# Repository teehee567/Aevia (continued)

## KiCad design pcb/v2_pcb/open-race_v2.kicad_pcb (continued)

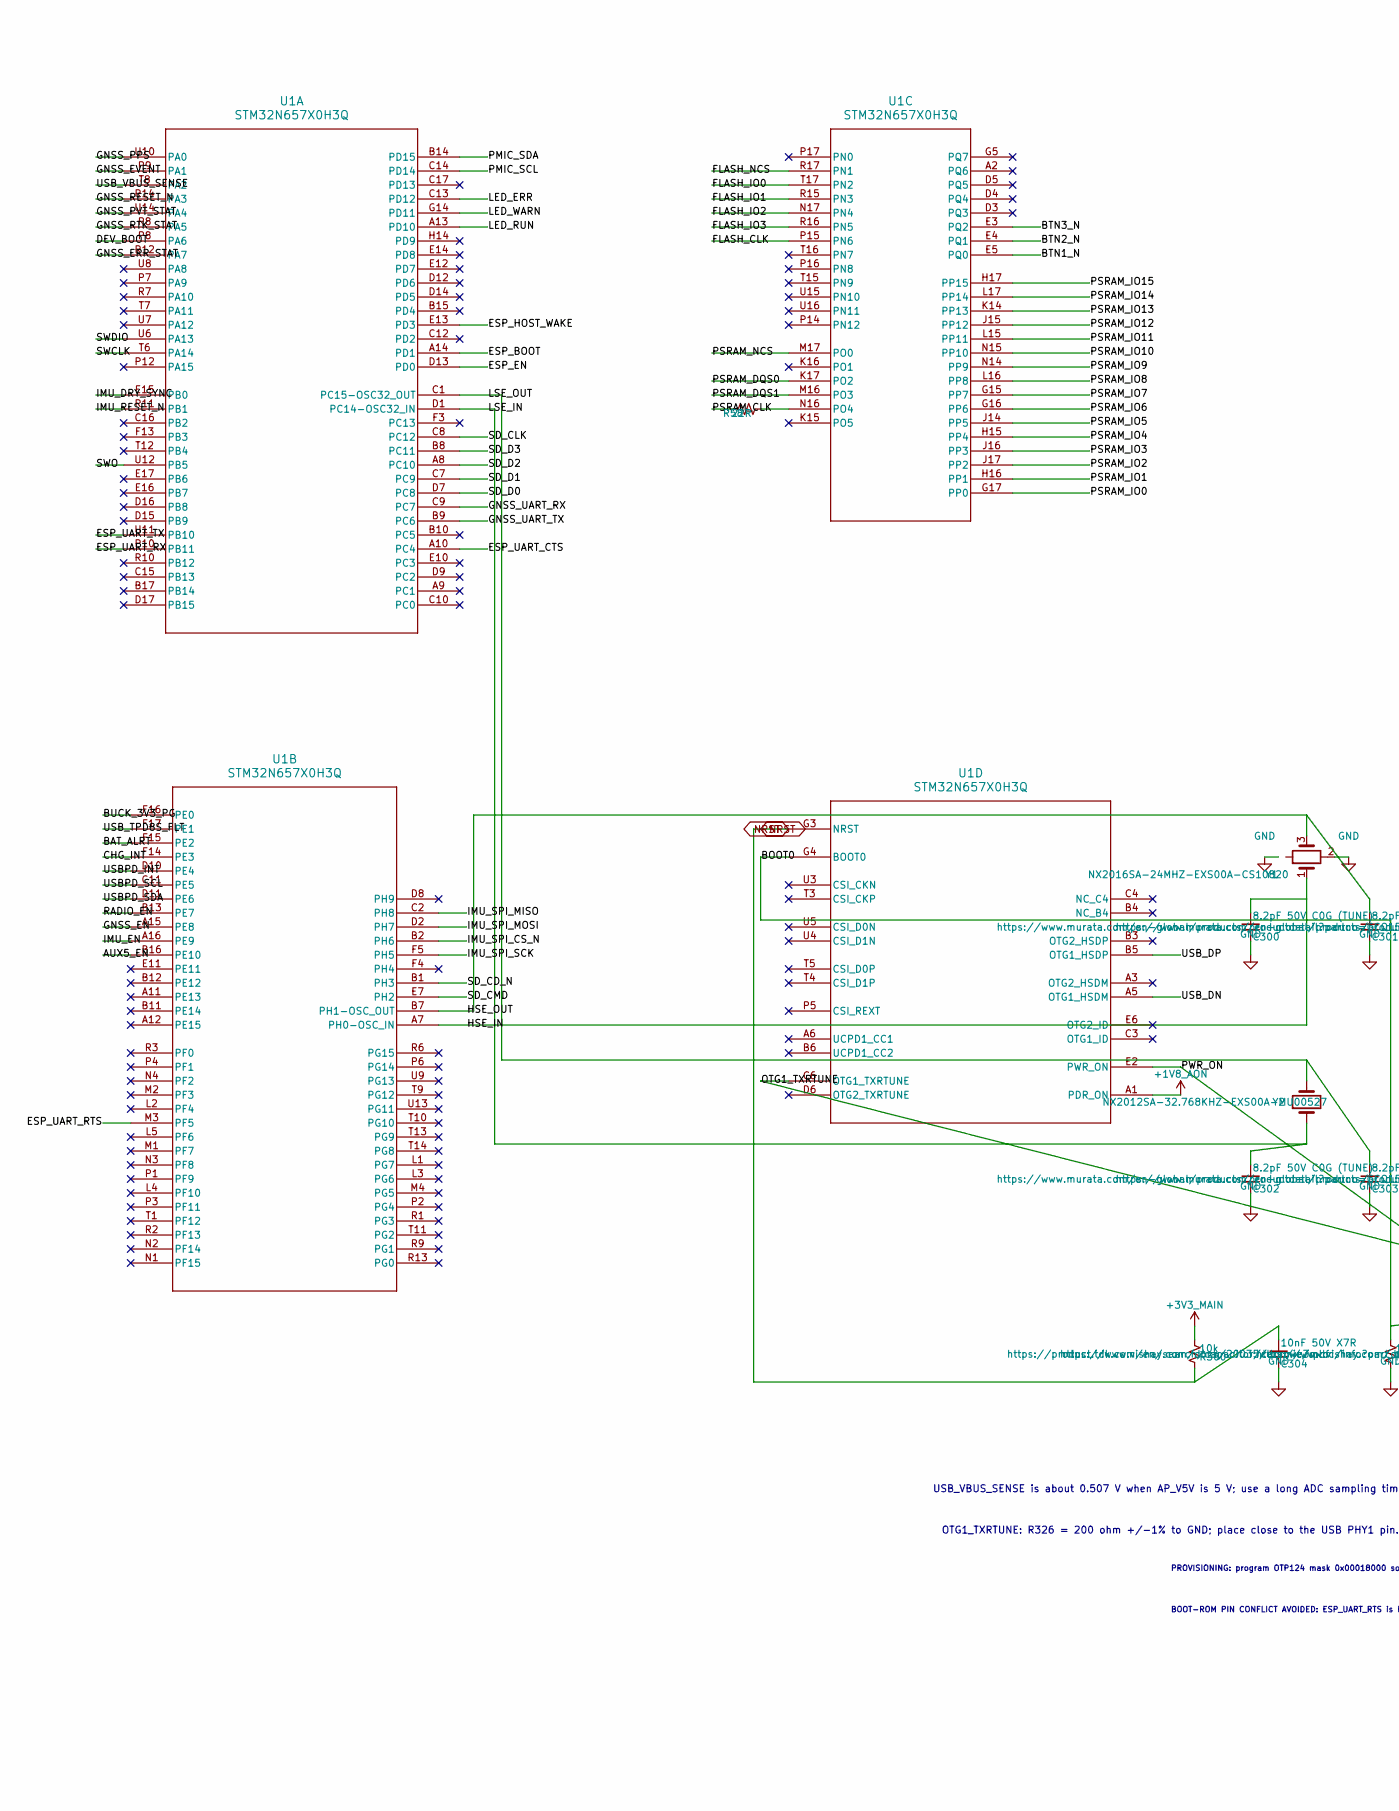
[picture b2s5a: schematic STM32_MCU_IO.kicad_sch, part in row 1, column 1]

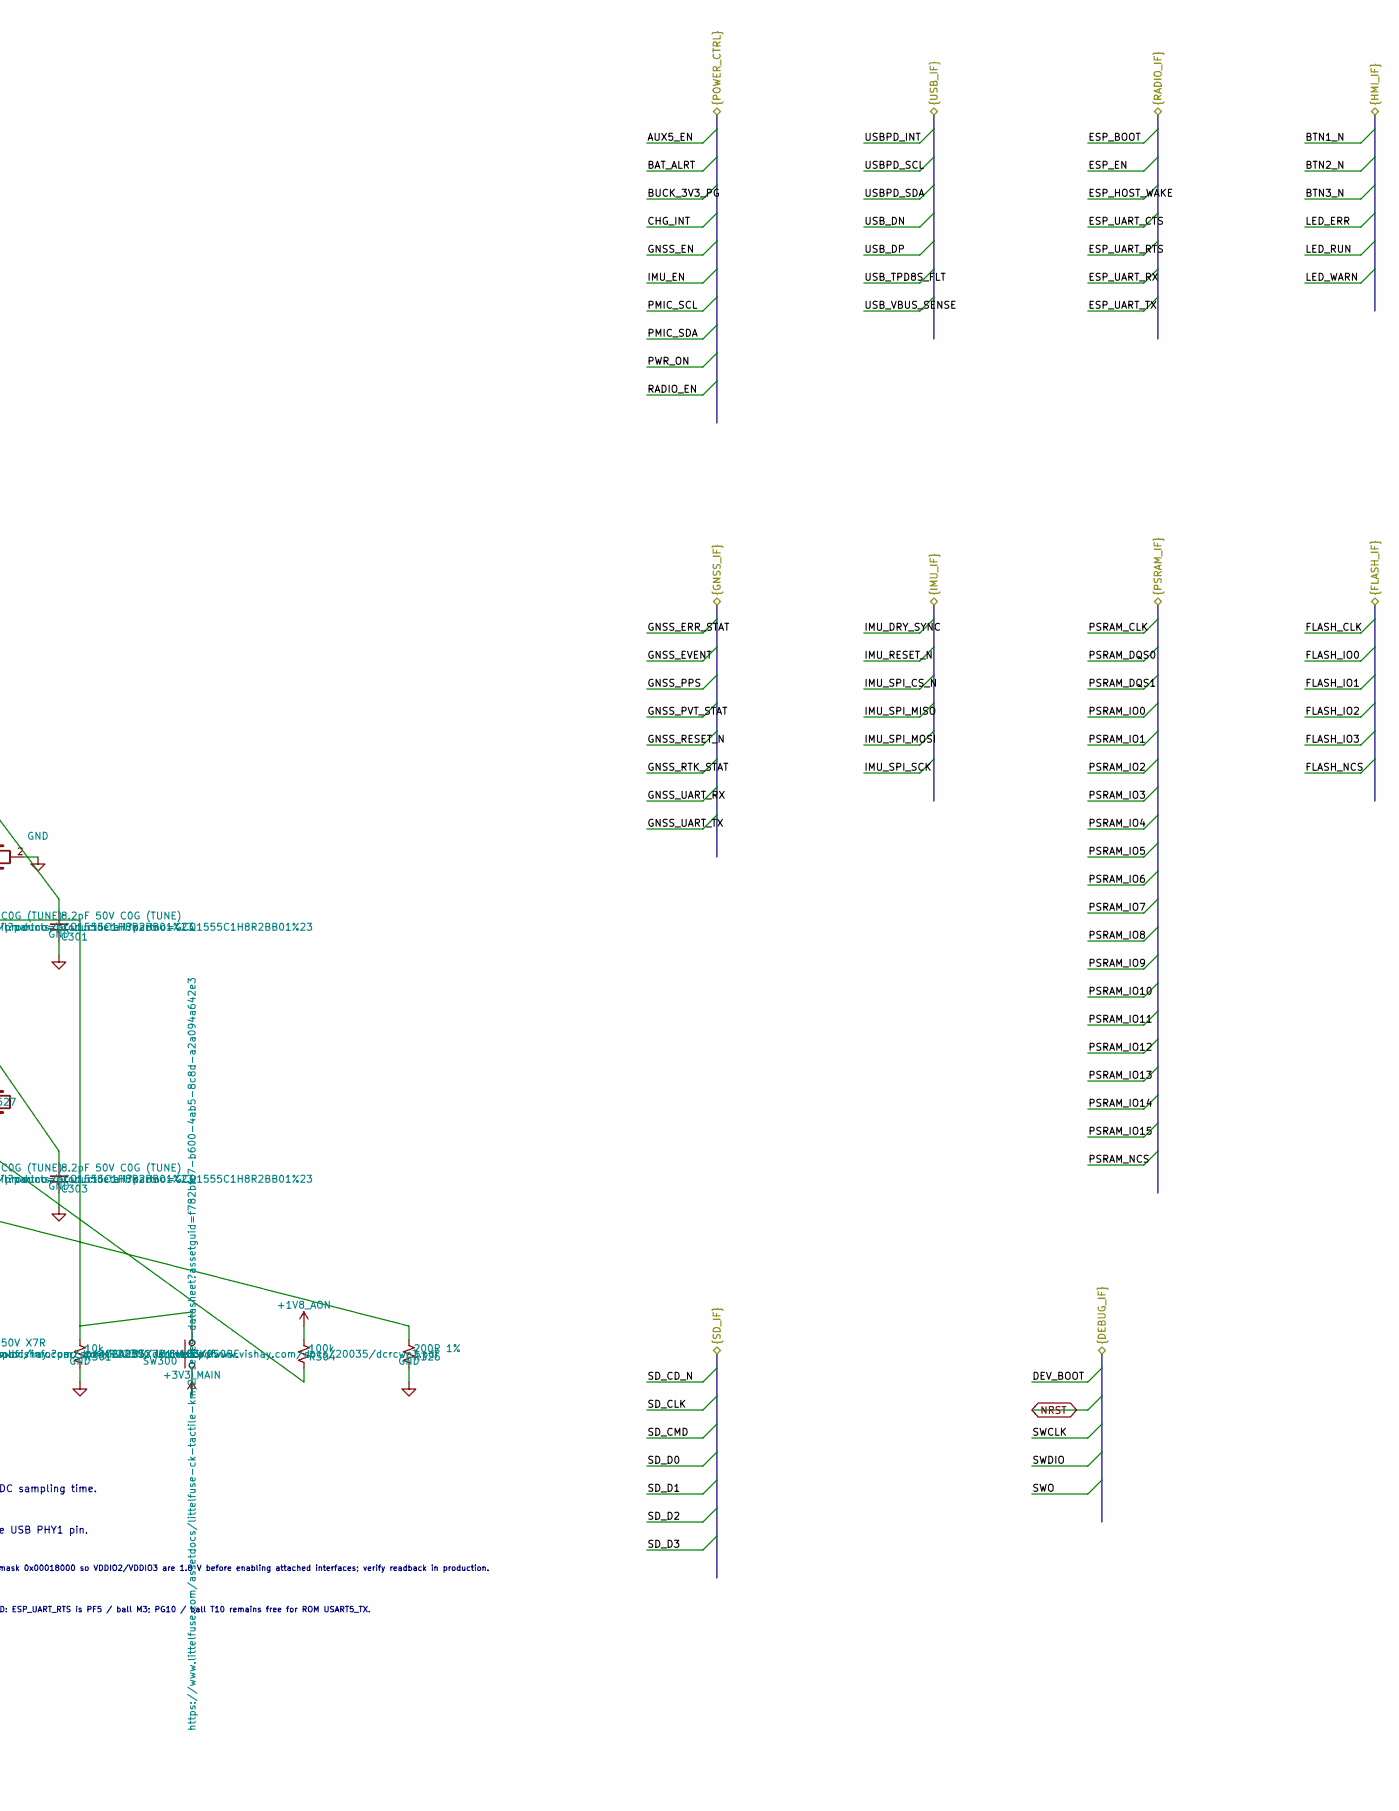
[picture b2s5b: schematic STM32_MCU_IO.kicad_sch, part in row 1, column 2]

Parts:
C300, C301, C302, C303: 8.2pF 50V C0G (TUNE); C_0402_1005Metric; Voltage 50 VDC; Tolerance ±0.1 pF; MPN GCQ1555C1H8R2BB01D
C304: 10nF 50V X7R; C_0402_1005Metric; Voltage 50 VDC; Tolerance ±10%; MPN CGA2B3X7R1H103K050BE
R58: 22R; R_0402_1005Metric; Tolerance ±1%; MPN CRCW040222R0FKED
R300, R301: 10k; R_0402_1005Metric; Tolerance ±1%; MPN CRCW040210K0FKED
R304: 100k; R_0402_1005Metric; Tolerance ±1%; MPN CRCW0402100KFKED
R326: 200R 1%; R_0402_1005Metric; Tolerance ±1%; MPN CRCW0402200RFKED
SW300: KMR223NG ULC LFG; SW_Push_1P1T_NO_CK_KMR2; MPN Y78B22324FP
U1: STM32N657X0H3Q; VFBGA264_14X14_STM; MPN STM32N657X0H3Q
Y1: NX2016SA-24MHZ-EXS00A-CS10820; Crystal_SMD_2016-4Pin_2.0x1.6mm; MPN NX2016SA-24MHZ-EXS00A-CS10820
Y2: NX2012SA-32.768KHZ-EXS00A-MU00527; Crystal_SMD_2012-2Pin_2.0x1.2mm; MPN NX2012SA-32.768KHZ-EXS00A-MU00527

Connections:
+1V8_AON: R304.1, U1.A1 (PDR_ON); also elsewhere on the board
/Buttons and LEDs/BTN1_N: U1.E5 (PQ0); also elsewhere on the board
/Buttons and LEDs/BTN2_N: U1.E4 (PQ1); also elsewhere on the board
/Buttons and LEDs/BTN3_N: U1.E3 (PQ2); also elsewhere on the board
/Buttons and LEDs/LED_ERR: U1.C13 (PD12); also elsewhere on the board
/Buttons and LEDs/LED_RUN: U1.A13 (PD10); also elsewhere on the board
/Buttons and LEDs/LED_WARN: U1.G14 (PD11); also elsewhere on the board
/ESP32-C6 radio/ESP_BOOT: U1.A14 (PD1); also elsewhere on the board
/ESP32-C6 radio/ESP_EN: U1.D13 (PD0); also elsewhere on the board
/ESP32-C6 radio/ESP_HOST_WAKE: U1.E13 (PD3); also elsewhere on the board
/ESP32-C6 radio/ESP_UART_CTS: U1.A10 (PC4); also elsewhere on the board
/ESP32-C6 radio/ESP_UART_RTS: U1.M3 (PF5); also elsewhere on the board
/ESP32-C6 radio/ESP_UART_RX: U1.P10 (PB11); also elsewhere on the board
/ESP32-C6 radio/ESP_UART_TX: U1.U11 (PB10); also elsewhere on the board
/Power/AUX5_EN: U1.B16 (PE10); also elsewhere on the board
/Power/BAT_ALRT: U1.F15 (PE2); also elsewhere on the board
/Power/BUCK_3V3_PG: U1.F16 (PE0); also elsewhere on the board
/Power/CHG_INT: U1.F14 (PE3); also elsewhere on the board
/Power/GNSS_EN: U1.A15 (PE8); also elsewhere on the board
/Power/IMU_EN: U1.A16 (PE9); also elsewhere on the board
/Power/PMIC_SCL: U1.C14 (PD14); also elsewhere on the board
/Power/PMIC_SDA: U1.B14 (PD15); also elsewhere on the board
/Power/PWR_ON: R304.2, U1.E2 (PWR_ON); also elsewhere on the board
/Power/RADIO_EN: U1.B13 (PE7); also elsewhere on the board
/Quad boot flash/FLASH_CLK: U1.P15 (PN6); also elsewhere on the board
/Quad boot flash/FLASH_IO0: U1.T17 (PN2); also elsewhere on the board
/Quad boot flash/FLASH_IO1: U1.R15 (PN3); also elsewhere on the board
/Quad boot flash/FLASH_IO2: U1.N17 (PN4); also elsewhere on the board
/Quad boot flash/FLASH_IO3: U1.R16 (PN5); also elsewhere on the board
/Quad boot flash/FLASH_NCS: U1.R17 (PN1); also elsewhere on the board
/SCH16T IMU/IMU_DRY_SYNC: U1.E15 (PB0); also elsewhere on the board
/SCH16T IMU/IMU_RESET_N: U1.R11 (PB1); also elsewhere on the board
/SCH16T IMU/IMU_SPI_CS_N: U1.B2 (PH6); also elsewhere on the board
/SCH16T IMU/IMU_SPI_MISO: U1.C2 (PH8); also elsewhere on the board
/SCH16T IMU/IMU_SPI_MOSI: U1.D2 (PH7); also elsewhere on the board
/SCH16T IMU/IMU_SPI_SCK: U1.F5 (PH5); also elsewhere on the board
/STM32 MCU IO/BOOT0: R301.1, SW300.2, U1.G4 (BOOT0)
/STM32 MCU IO/DEV_BOOT: U1.P8 (PA6); also elsewhere on the board
/STM32 MCU IO/GNSS_ERR_STAT: U1.R12 (PA7); also elsewhere on the board
/STM32 MCU IO/GNSS_EVENT: U1.P9 (PA1); also elsewhere on the board
/STM32 MCU IO/GNSS_PPS: U1.U10 (PA0); also elsewhere on the board
/STM32 MCU IO/GNSS_PVT_STAT: U1.U14 (PA4); also elsewhere on the board
/STM32 MCU IO/GNSS_RESET_N: U1.R14 (PA3); also elsewhere on the board
/STM32 MCU IO/GNSS_RTK_STAT: U1.R8 (PA5); also elsewhere on the board
/STM32 MCU IO/GNSS_UART_RX: U1.C9 (PC7); also elsewhere on the board
/STM32 MCU IO/GNSS_UART_TX: U1.B9 (PC6); also elsewhere on the board
/STM32 MCU IO/HSE_IN: C300.1, U1.A7 (PH0-OSC_IN), Y1.1
/STM32 MCU IO/HSE_OUT: C301.1, U1.B7 (PH1-OSC_OUT), Y1.3
/STM32 MCU IO/LSE_IN: C302.1, U1.D1 (PC14-OSC32_IN), Y2.1
/STM32 MCU IO/LSE_OUT: C303.1, U1.C1 (PC15-OSC32_OUT), Y2.2
/STM32 MCU IO/PSRAM_CLK: R58.1; also elsewhere on the board
/STM32 MCU IO/PSRAM_DQS0: U1.K17 (PO2); also elsewhere on the board
/STM32 MCU IO/PSRAM_DQS1: U1.M16 (PO3); also elsewhere on the board
/STM32 MCU IO/PSRAM_IO0: U1.G17 (PP0); also elsewhere on the board
/STM32 MCU IO/PSRAM_IO1: U1.H16 (PP1); also elsewhere on the board
/STM32 MCU IO/PSRAM_IO2: U1.J17 (PP2); also elsewhere on the board
/STM32 MCU IO/PSRAM_IO3: U1.J16 (PP3); also elsewhere on the board
/STM32 MCU IO/PSRAM_IO4: U1.H15 (PP4); also elsewhere on the board
/STM32 MCU IO/PSRAM_IO5: U1.J14 (PP5); also elsewhere on the board
/STM32 MCU IO/PSRAM_IO6: U1.G16 (PP6); also elsewhere on the board
/STM32 MCU IO/PSRAM_IO7: U1.G15 (PP7); also elsewhere on the board
/STM32 MCU IO/PSRAM_IO8: U1.L16 (PP8); also elsewhere on the board
/STM32 MCU IO/PSRAM_IO9: U1.N14 (PP9); also elsewhere on the board
/STM32 MCU IO/PSRAM_IO10: U1.N15 (PP10); also elsewhere on the board
/STM32 MCU IO/PSRAM_IO11: U1.L15 (PP11); also elsewhere on the board
/STM32 MCU IO/PSRAM_IO12: U1.J15 (PP12); also elsewhere on the board
/STM32 MCU IO/PSRAM_IO13: U1.K14 (PP13); also elsewhere on the board
/STM32 MCU IO/PSRAM_IO14: U1.L17 (PP14); also elsewhere on the board
/STM32 MCU IO/PSRAM_IO15: U1.H17 (PP15); also elsewhere on the board
/STM32 MCU IO/PSRAM_NCS: U1.M17 (PO0); also elsewhere on the board
/STM32 MCU IO/SD_CD_N: U1.B1 (PH3); also elsewhere on the board
/STM32 MCU IO/SD_CLK: U1.C8 (PC12); also elsewhere on the board
/STM32 MCU IO/SD_CMD: U1.E7 (PH2); also elsewhere on the board
/STM32 MCU IO/SD_D0: U1.D7 (PC8); also elsewhere on the board
/STM32 MCU IO/SD_D1: U1.C7 (PC9); also elsewhere on the board
/STM32 MCU IO/SD_D2: U1.A8 (PC10); also elsewhere on the board
/STM32 MCU IO/SD_D3: U1.B8 (PC11); also elsewhere on the board
/STM32 MCU IO/SWCLK: U1.T6 (PA14); also elsewhere on the board
/STM32 MCU IO/SWDIO: U1.U6 (PA13); also elsewhere on the board
/STM32 MCU IO/SWO: U1.U12 (PB5); also elsewhere on the board
/STM32 MCU IO/USBPD_INT: U1.D10 (PE4); also elsewhere on the board
/STM32 MCU IO/USBPD_SCL: U1.C11 (PE5); also elsewhere on the board
/STM32 MCU IO/USBPD_SDA: U1.D11 (PE6); also elsewhere on the board
/STM32 MCU IO/USB_DN: U1.A5 (OTG1_HSDM); also elsewhere on the board
/STM32 MCU IO/USB_DP: U1.B5 (OTG1_HSDP); also elsewhere on the board
/STM32 MCU IO/USB_TPD8S_FLT: U1.F17 (PE1); also elsewhere on the board
/STM32 MCU IO/USB_VBUS_SENSE: U1.T8 (PA2); also elsewhere on the board
NRST: C304.1, R300.2, U1.G3 (NRST); also elsewhere on the board
unnamed: R58.2, U1.N16 (PO4)

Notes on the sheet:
BOOT-ROM PIN CONFLICT AVOIDED: ESP_UART_RTS is PF5 / ball M3; PG10 / ball T10 remains free for ROM USART5_TX.
PROVISIONING: program OTP124 mask 0x00018000 so VDDIO2/VDDIO3 are 1.8 V before enabling attached interfaces; verify readback in production.
OTG1_TXRTUNE: R326 = 200 ohm +/-1% to GND; place close to the USB PHY1 pin.
USB_VBUS_SENSE is about 0.507 V when AP_V5V is 5 V; use a long ADC sampling time.

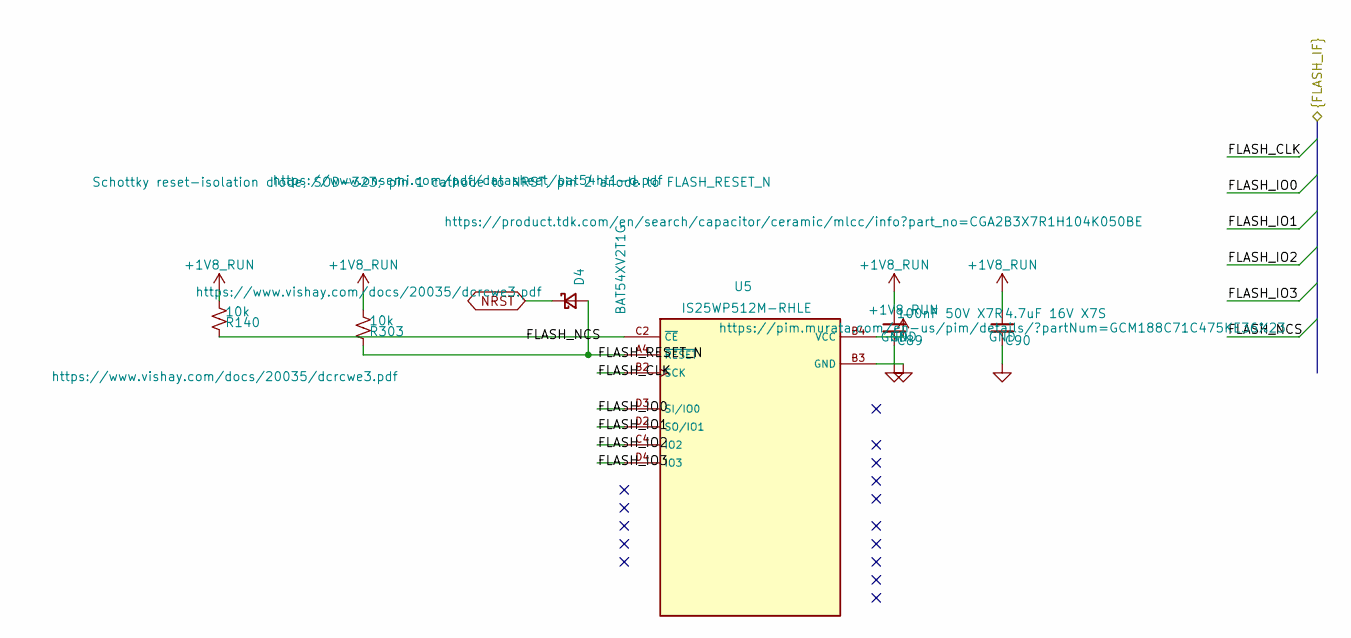
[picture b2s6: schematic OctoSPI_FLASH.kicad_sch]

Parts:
C89: 100nF 50V X7R; C_0402_1005Metric; Voltage 50 VDC; Tolerance ±10%; MPN CGA2B3X7R1H104K050BE
C90: 4.7uF 16V X7S; C_0603_1608Metric; Voltage 16 VDC; Tolerance ±10%; MPN GCM188C71C475KE36D
D4: BAT54XV2T1G; D_SOD-523; MPN BAT54HT1G
R140, R303: 10k; R_0402_1005Metric; Tolerance ±1%; MPN CRCW040210K0FKED
U5: IS25WP512M-RHLE; BGA24C100P5X5_800X600X120; MPN IS25WP512M-RHLE

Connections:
+1V8_RUN: C89.1, C90.1, R140.1, R303.1, U5.B4 (VCC); also elsewhere on the board
/Quad boot flash/FLASH_CLK: U5.B2 (SCK); also elsewhere on the board
/Quad boot flash/FLASH_IO0: U5.D3 (SI/IO0); also elsewhere on the board
/Quad boot flash/FLASH_IO1: U5.D2 (SO/IO1); also elsewhere on the board
/Quad boot flash/FLASH_IO2: U5.C4 (IO2); also elsewhere on the board
/Quad boot flash/FLASH_IO3: U5.D4 (IO3); also elsewhere on the board
/Quad boot flash/FLASH_NCS: R140.2, U5.C2 (~CE); also elsewhere on the board
/Quad boot flash/FLASH_RESET_N: D4.2 (A), R303.2, U5.A4 (~RESET)
NRST: D4.1 (K); also elsewhere on the board

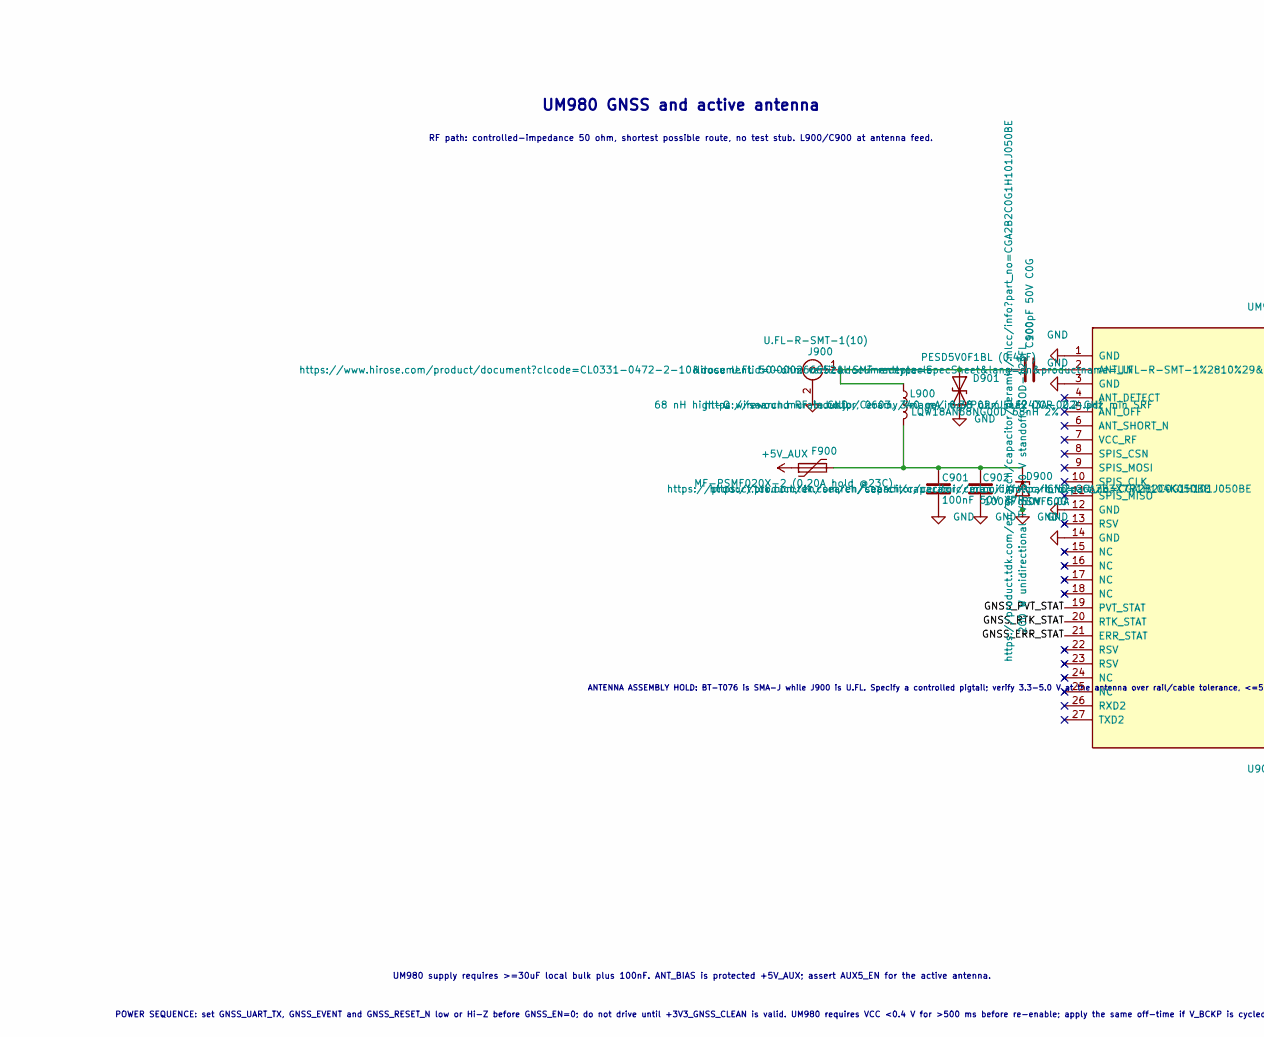
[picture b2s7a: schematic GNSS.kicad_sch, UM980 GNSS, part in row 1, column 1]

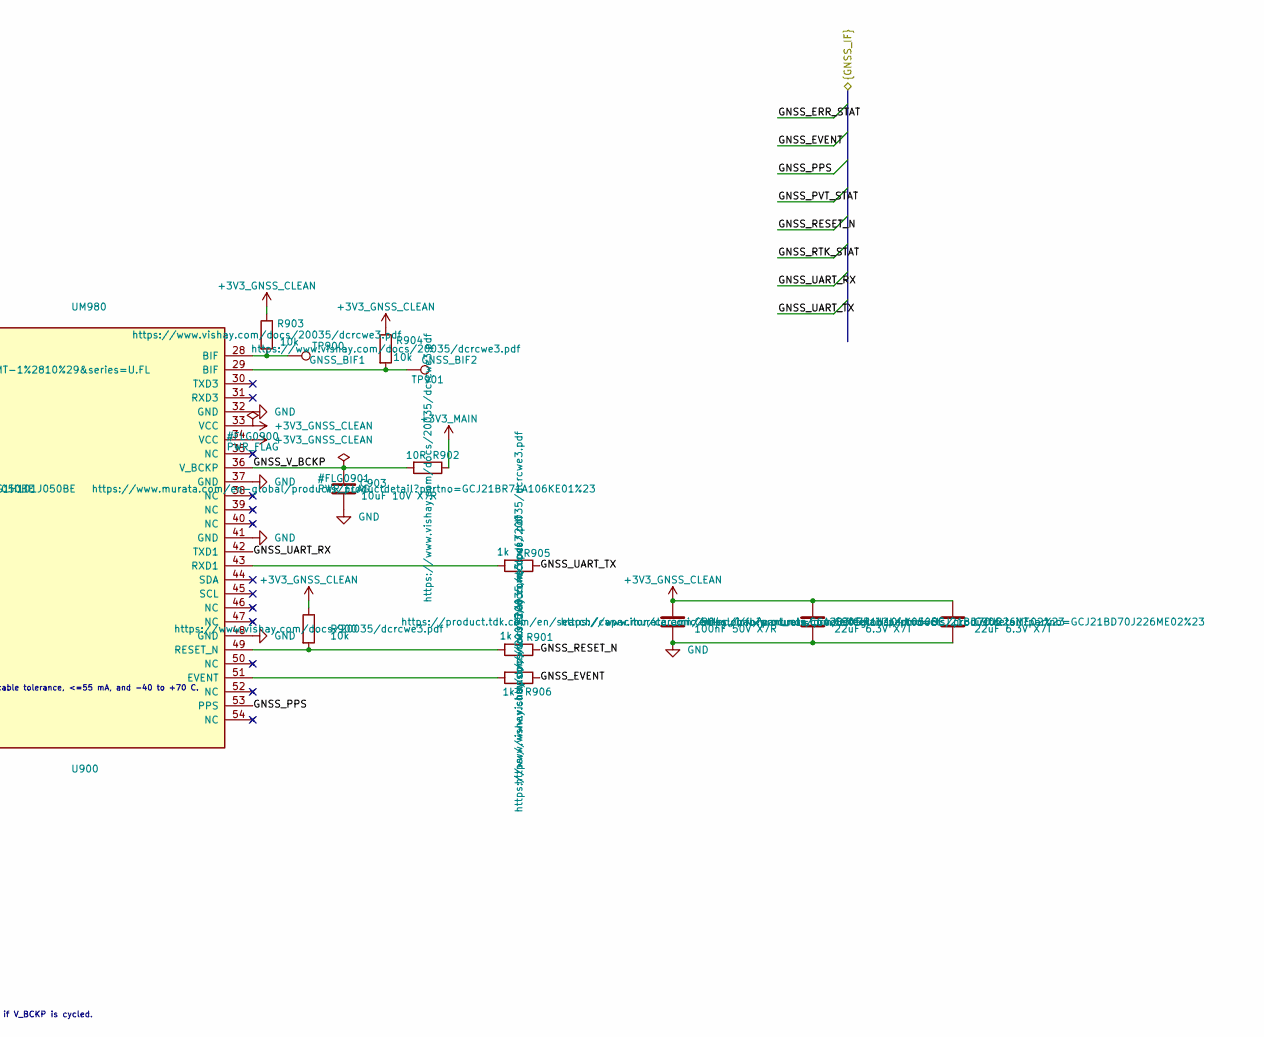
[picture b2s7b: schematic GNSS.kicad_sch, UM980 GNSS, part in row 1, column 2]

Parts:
C900, C902: 100pF 50V C0G; C_0402_1005Metric; Voltage 50 VDC; Tolerance ±5%; MPN CGA2B2C0G1H101J050BE
C901, C904: 100nF 50V X7R; C_0402_1005Metric; Voltage 50 VDC; Tolerance ±10%; MPN CGA2B3X7R1H104K050BE
C903: 10uF 10V X7R; C_0805_2012Metric; Voltage 10 VDC; Tolerance ±10%; MPN GCJ21BR71A106KE01L
C905, C906: 22uF 6.3V X7T; C_0805_2012Metric; Voltage 6.3 VDC; Tolerance ±20%; MPN GCJ21BD70J226ME02L
D900: SMF5.0A; SOD-123FL_Littelfuse_SMF; MPN SMF5.0A
D901: PESD5V0F1BL (0.4pF); D_SOD-882; MPN PESD5V0F1BL,315
F900: MF-PSMF020X-2 (0.20A hold @23C); Fuse_0805_2012Metric; MPN MF-PSMF020X-2
J900: U.FL-R-SMT-1(10); U.FL_Hirose_U.FL-R-SMT-1_Vertical; MPN U.FL-R-SMT-1(10)
L900: LQW18AN68NG00D 68nH 2%; L_0603_1608Metric; MPN LQW18AN68NG00D
R900, R903, R904: 10k; R_0402_1005Metric; Tolerance ±1%; MPN CRCW040210K0FKED
R901, R905, R906: 1k; R_0402_1005Metric; Tolerance ±1%; MPN CRCW04021K00FKED
R902: 10R; R_0402_1005Metric; Tolerance ±1%; MPN CRCW040210R0FKED
TP900: GNSS_BIF1; TestPoint_Pad_D1.0mm
TP901: GNSS_BIF2; TestPoint_Pad_D1.0mm
U900: UM980; UM980_LGA-54_17x22mm; MPN UM980

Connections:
+3V3_GNSS_CLEAN: C904.1, C905.1, C906.1, R900.1, R903.1, R904.1, U900.33 (VCC), U900.34 (VCC); also elsewhere on the board
+5V_AUX: F900.1; also elsewhere on the board
/STM32 MCU IO/GNSS_ERR_STAT: U900.21 (ERR_STAT); also elsewhere on the board
/STM32 MCU IO/GNSS_EVENT: R906.1; also elsewhere on the board
/STM32 MCU IO/GNSS_PPS: U900.53 (PPS); also elsewhere on the board
/STM32 MCU IO/GNSS_PVT_STAT: U900.19 (PVT_STAT); also elsewhere on the board
/STM32 MCU IO/GNSS_RESET_N: R901.1; also elsewhere on the board
/STM32 MCU IO/GNSS_RTK_STAT: U900.20 (RTK_STAT); also elsewhere on the board
/STM32 MCU IO/GNSS_UART_RX: U900.42 (TXD1); also elsewhere on the board
/STM32 MCU IO/GNSS_UART_TX: R905.1; also elsewhere on the board
/UM980 GNSS/GNSS_V_BCKP: C903.1, R902.2, U900.36 (V_BCKP)
unnamed: C901.1, C902.1, D900.1 (K), F900.2, L900.2
unnamed: C900.1, D901.1 (A1), J900.1 (In), L900.1
unnamed: R903.2, TP900.1 (1_1), U900.28 (BIF)
unnamed: R904.2, TP901.1 (1_1), U900.29 (BIF)
unnamed: C900.2, U900.2 (ANT_IN)
unnamed: R906.2, U900.51 (EVENT)
unnamed: R900.2, R901.2, U900.49 (RESET_N)
unnamed: R905.2, U900.43 (RXD1)

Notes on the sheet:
POWER SEQUENCE: set GNSS_UART_TX, GNSS_EVENT and GNSS_RESET_N low or Hi-Z before GNSS_EN=0; do not drive until +3V3_GNSS_CLEAN is valid. UM980 requires VCC <0.4 V for >500 ms before re-enable; apply the same off-time if V_BCKP is cycled.
RF path: controlled-impedance 50 ohm, shortest possible route, no test stub. L900/C900 at antenna feed.
UM980 supply requires >=30uF local bulk plus 100nF. ANT_BIAS is protected +5V_AUX; assert AUX5_EN for the active antenna.
UM980 GNSS and active antenna
ANTENNA ASSEMBLY HOLD: BT-T076 is SMA-J while J900 is U.FL. Specify a controlled pigtail; verify 3.3-5.0 V at the antenna over rail/cable tolerance, <=55 mA, and -40 to +70 C.

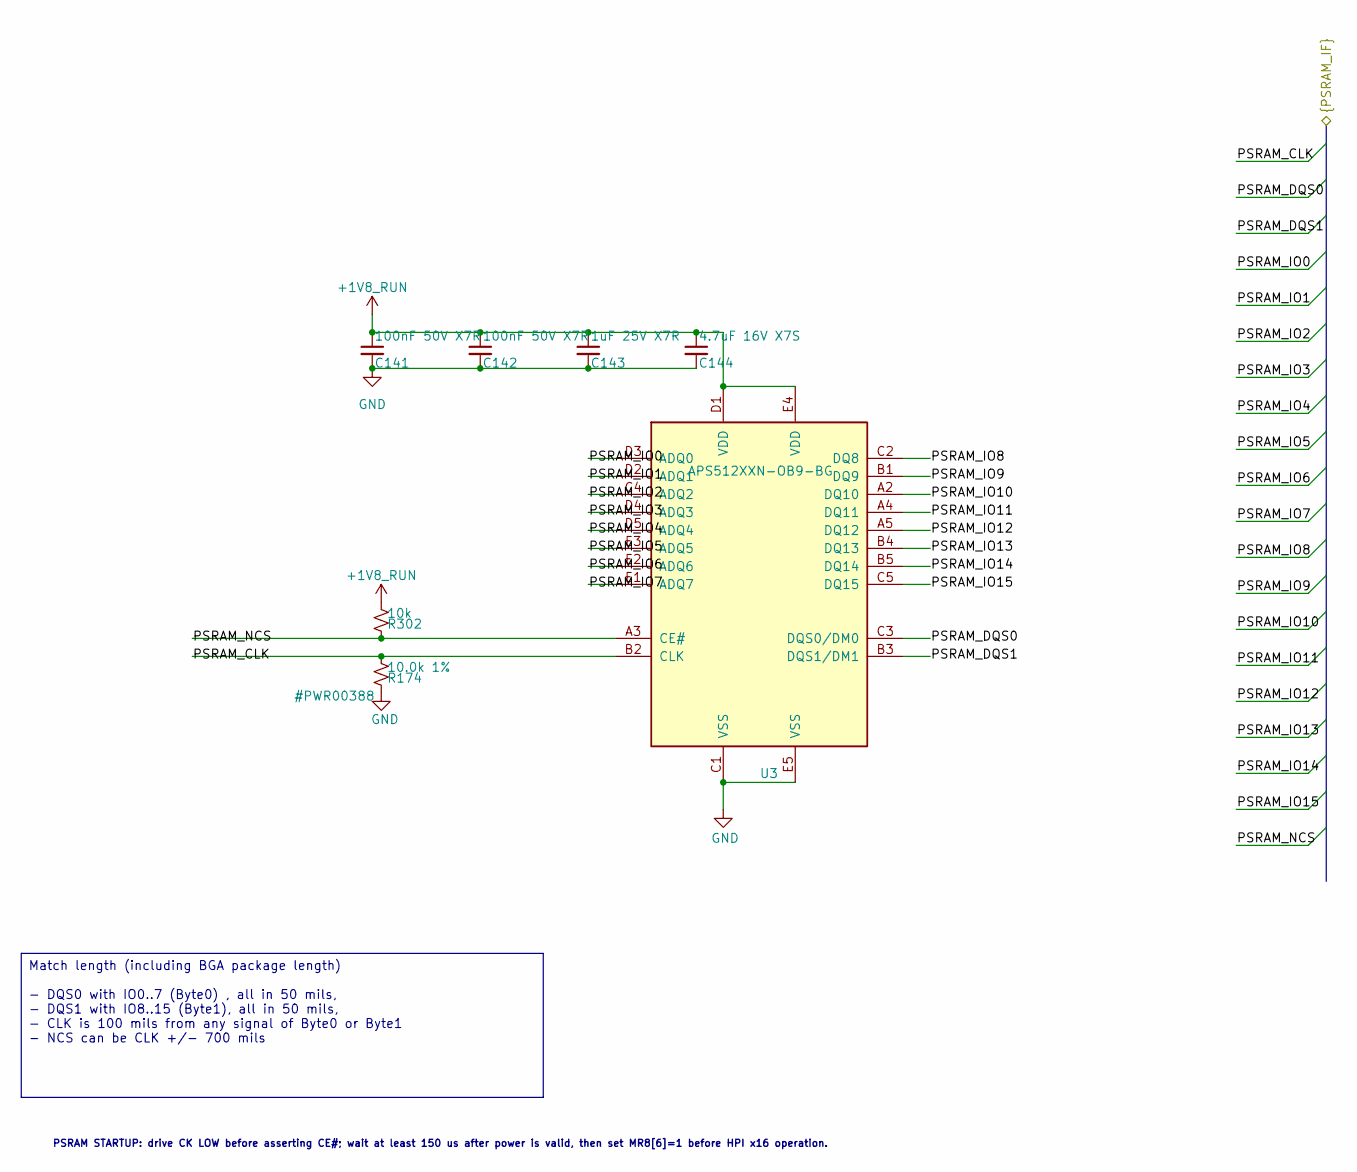
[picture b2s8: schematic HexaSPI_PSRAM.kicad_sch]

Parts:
C141, C142: 100nF 50V X7R; C_0402_1005Metric; Voltage 50 VDC; Tolerance ±10%; MPN CGA2B3X7R1H104K050BE
C143: 1uF 25V X7R; C_0603_1608Metric; Voltage 25 VDC; Tolerance ±10%; MPN CGA3E1X7R1E105K080AE
C144: 4.7uF 16V X7S; C_0603_1608Metric; Voltage 16 VDC; Tolerance ±10%; MPN GCM188C71C475KE36D
R174: 10.0k 1%; R_0402_1005Metric; Tolerance ±1%; MPN CRCW040210K0FKED
R302: 10k; R_0402_1005Metric; Tolerance ±1%; MPN CRCW040210K0FKED
U3: APS512XXN-OB9-BG; WLCSP-24_6x8mm_P1.0mm_APS512XXN; MPN APS512XXN-OB9-BG

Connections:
+1V8_RUN: C141.1, C142.1, C143.1, C144.1, R302.1, U3.D1 (VDD), U3.E4 (VDD); also elsewhere on the board
/STM32 MCU IO/PSRAM_CLK: R174.1, U3.B2 (CLK); also elsewhere on the board
/STM32 MCU IO/PSRAM_DQS0: U3.C3 (DQS0/DM0); also elsewhere on the board
/STM32 MCU IO/PSRAM_DQS1: U3.B3 (DQS1/DM1); also elsewhere on the board
/STM32 MCU IO/PSRAM_IO0: U3.D3 (ADQ0); also elsewhere on the board
/STM32 MCU IO/PSRAM_IO1: U3.D2 (ADQ1); also elsewhere on the board
/STM32 MCU IO/PSRAM_IO2: U3.C4 (ADQ2); also elsewhere on the board
/STM32 MCU IO/PSRAM_IO3: U3.D4 (ADQ3); also elsewhere on the board
/STM32 MCU IO/PSRAM_IO4: U3.D5 (ADQ4); also elsewhere on the board
/STM32 MCU IO/PSRAM_IO5: U3.E3 (ADQ5); also elsewhere on the board
/STM32 MCU IO/PSRAM_IO6: U3.E2 (ADQ6); also elsewhere on the board
/STM32 MCU IO/PSRAM_IO7: U3.E1 (ADQ7); also elsewhere on the board
/STM32 MCU IO/PSRAM_IO8: U3.C2 (DQ8); also elsewhere on the board
/STM32 MCU IO/PSRAM_IO9: U3.B1 (DQ9); also elsewhere on the board
/STM32 MCU IO/PSRAM_IO10: U3.A2 (DQ10); also elsewhere on the board
/STM32 MCU IO/PSRAM_IO11: U3.A4 (DQ11); also elsewhere on the board
/STM32 MCU IO/PSRAM_IO12: U3.A5 (DQ12); also elsewhere on the board
/STM32 MCU IO/PSRAM_IO13: U3.B4 (DQ13); also elsewhere on the board
/STM32 MCU IO/PSRAM_IO14: U3.B5 (DQ14); also elsewhere on the board
/STM32 MCU IO/PSRAM_IO15: U3.C5 (DQ15); also elsewhere on the board
/STM32 MCU IO/PSRAM_NCS: R302.2, U3.A3 (CE#); also elsewhere on the board

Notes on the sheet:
PSRAM STARTUP: drive CK LOW before asserting CE#; wait at least 150 us after power is valid, then set MR8[6]=1 before HPI x16 operation.
Match length (including BGA package length) - DQS0 with IO0..7 (Byte0) , all in 50 mils, - DQS1 with IO8..15 (Byte1), all in 50 mils, - CLK is 100 mils from any signal of Byte0 or Byte1 - NCS can be CLK +/- 700 mils

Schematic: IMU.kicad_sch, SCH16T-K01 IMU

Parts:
C1000, C1003: 1uF 25V X7R; C_0603_1608Metric; Voltage 25 VDC; Tolerance ±10%; MPN CGA3E1X7R1E105K080AE
C1001: 10uF 10V X7R; C_0805_2012Metric; Voltage 10 VDC; Tolerance ±10%; MPN GCJ21BR71A106KE01L
C1002, C1004: 100nF 50V X7R; C_0402_1005Metric; Voltage 50 VDC; Tolerance ±10%; MPN CGA2B3X7R1H104K050BE
R1000: 10k; R_0402_1005Metric; Tolerance ±1%; MPN CRCW040210K0FKED
R1001: 100R; R_0402_1005Metric; Tolerance ±1%; MPN CRCW0402100RFKED
R1002, R1004, R1005, R1006: 22R; R_0402_1005Metric; Tolerance ±1%; MPN CRCW040222R0FKED
R1003: 33R; R_0402_1005Metric; Tolerance ±1%; MPN CRCW040233R0FKED
U1000: SCH16T-K01-1; SOIC-24_SCH16T_11.8x13.4mm; MPN SCH16T-K01-1

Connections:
+3V3_IMU_CLEAN: C1002.1, C1003.1, C1004.1, R1000.1, U1000.8 (V3P3), U1000.17 (V3P3), U1000.18 (VDDIO); also elsewhere on the board
/SCH16T IMU/IMU_DRY_SYNC: R1003.1; also elsewhere on the board
/SCH16T IMU/IMU_RESET_N: R1001.1; also elsewhere on the board
/SCH16T IMU/IMU_SPI_CS_N: R1005.1; also elsewhere on the board
/SCH16T IMU/IMU_SPI_MISO: R1002.1; also elsewhere on the board
/SCH16T IMU/IMU_SPI_MOSI: R1006.1; also elsewhere on the board
/SCH16T IMU/IMU_SPI_SCK: R1004.1; also elsewhere on the board
unnamed: R1005.2, U1000.22 (CS)
unnamed: R1003.2, U1000.20 (DRY_SYNC)
unnamed: R1000.2, R1001.2, U1000.6 (EXTRESN)
unnamed: R1002.2, U1000.19 (MISO)
unnamed: R1006.2, U1000.23 (MOSI)
unnamed: R1004.2, U1000.21 (SCK)
unnamed: C1001.1, U1000.10 (VREGA2), U1000.11 (VREGA)
unnamed: C1000.1, U1000.14 (VREGD2), U1000.15 (VREGD)

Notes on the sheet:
SCH16T-K01 high-performance IMU
Keep regulator capacitors at their pin pairs; join exposed/heat-sink pads to the quiet ground plane.
Datasheet bypass: VREGD/VREGD2 1uF; VREGA/VREGA2 10uF; V3P3 pin 8 100nF; V3P3 pin 17 1uF.
POWER SEQUENCE: make IMU SPI SCK/MOSI/CS, DRY_SYNC and RESET_N analog/Hi-Z before IMU_EN=0; do not drive until +3V3_IMU_CLEAN is valid.

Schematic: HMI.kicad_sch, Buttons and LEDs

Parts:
C1100, C1101, C1110, C1111, C1112, C1113, C1114, C1121, C1122, C1123: 100nF 50V X7R; C_0402_1005Metric; Voltage 50 VDC; Tolerance ±10%; MPN CGA2B3X7R1H104K050BE
C1115: 47uF 10V X7R; C_1210_3225Metric; Voltage 10 VDC; Tolerance ±10%; MPN C1210X476K8RACAUTO
D1100, D1101, D1102, D1103, D1104: APA102-2020-256-8; LED-APA102-2020; MPN APA102-2020-256-8
D1110: ASMT-RF45-AN002 YELLOW GREEN; LED_0603_1608Metric; MPN ASMT-RF45-AN002
D1111: ASMT-RJ45-AQ502 ORANGE; LED_0603_1608Metric; MPN ASMT-RJ45-AQ502
D1112: ASMT-RR45-AQ902 RED; LED_0603_1608Metric; MPN ASMT-RR45-AQ902
R1100, R1101: 33R; R_0402_1005Metric; Tolerance ±1%; MPN CRCW040233R0FKED
R1102, R1103, R1121, R1122, R1123: 10k; R_0402_1005Metric; Tolerance ±1%; MPN CRCW040210K0FKED
R1110, R1111, R1112: 1k; R_0402_1005Metric; Tolerance ±1%; MPN CRCW04021K00FKED
SW1101, SW1102, SW1103: KMR223NG ULC LFG; SW_Push_1P1T_NO_CK_KMR2; MPN Y78B22324FP
U1100, U1101: SN74AHCT1G125DCKR; SOT-353_SC-70-5; MPN SN74AHCT1G125DCKR

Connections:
+5V_AUX: C1100.1, C1101.1, C1110.1, C1111.1, C1112.1, C1113.1, C1114.1, C1115.1, D1100.1 (VDD), D1101.1 (VDD), D1102.1 (VDD), D1103.1 (VDD), D1104.1 (VDD), U1100.5 (VCC), U1101.5 (VCC); also elsewhere on the board
/Buttons and LEDs/APA_CLK_1_2: D1100.2 (CKO), D1101.5 (CKI)
/Buttons and LEDs/APA_CLK_2_3: D1101.2 (CKO), D1102.5 (CKI)
/Buttons and LEDs/APA_CLK_3_4: D1102.2 (CKO), D1103.5 (CKI)
/Buttons and LEDs/APA_CLK_4_5: D1103.2 (CKO), D1104.5 (CKI)
/Buttons and LEDs/APA_CLK_5V: D1100.5 (CKI), R1101.1
/Buttons and LEDs/APA_CLK_BUF: R1101.2, U1101.4
/Buttons and LEDs/APA_DATA_1_2: D1100.3 (SDO), D1101.4 (SDI)
/Buttons and LEDs/APA_DATA_2_3: D1101.3 (SDO), D1102.4 (SDI)
/Buttons and LEDs/APA_DATA_3_4: D1102.3 (SDO), D1103.4 (SDI)
/Buttons and LEDs/APA_DATA_4_5: D1103.3 (SDO), D1104.4 (SDI)
/Buttons and LEDs/APA_DATA_5V: D1100.4 (SDI), R1100.1
/Buttons and LEDs/APA_DATA_BUF: R1100.2, U1100.4
/Buttons and LEDs/BTN1_N: C1121.1, R1121.2, SW1101.1; also elsewhere on the board
/Buttons and LEDs/BTN2_N: C1122.1, R1122.2, SW1102.1; also elsewhere on the board
/Buttons and LEDs/BTN3_N: C1123.1, R1123.2, SW1103.1; also elsewhere on the board
/Buttons and LEDs/ESP_APA_CLK: R1103.1, U1101.2; also elsewhere on the board
/Buttons and LEDs/ESP_APA_DATA: R1102.1, U1100.2; also elsewhere on the board
/Buttons and LEDs/LED_ERR: R1112.2; also elsewhere on the board
/Buttons and LEDs/LED_ERR_ANODE: D1112.2 (A), R1112.1
/Buttons and LEDs/LED_RUN: R1110.2; also elsewhere on the board
/Buttons and LEDs/LED_RUN_ANODE: D1110.2 (A), R1110.1
/Buttons and LEDs/LED_WARN: R1111.2; also elsewhere on the board
/Buttons and LEDs/LED_WARN_ANODE: D1111.2 (A), R1111.1

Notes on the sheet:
AHCT inputs accept 3.3 V logic while powered at 5 V. Route clock and data together and keep the first pixel close to U1100/U1101.
Buttons and LEDs (no display, no buzzer)

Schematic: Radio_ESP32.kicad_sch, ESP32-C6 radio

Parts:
C800: 1uF 25V X7R; C_0603_1608Metric; Voltage 25 VDC; Tolerance ±10%; MPN CGA3E1X7R1E105K080AE
C801: 100nF 50V X7R; C_0402_1005Metric; Voltage 50 VDC; Tolerance ±10%; MPN CGA2B3X7R1H104K050BE
C802: 10uF 10V X7R; C_0805_2012Metric; Voltage 10 VDC; Tolerance ±10%; MPN GCJ21BR71A106KE01L
C803: 47uF 10V X7R; C_1210_3225Metric; Voltage 10 VDC; Tolerance ±10%; MPN C1210X476K8RACAUTO
J800: M50-3530642 (VTREF sense only); PinHeader_1x06_P1.27mm_Vertical; MPN M50-3530642
R800, R802, R804: 10k; R_0402_1005Metric; Tolerance ±1%; MPN CRCW040210K0FKED
R801, R803, R805, R806: 1k; R_0402_1005Metric; Tolerance ±1%; MPN CRCW04021K00FKED
R807: 10k VTREF isolation; R_0402_1005Metric; Tolerance ±1%; MPN CRCW040210K0FKED
SW800, SW801: KMR223NG ULC LFG; SW_Push_1P1T_NO_CK_KMR2; MPN Y78B22324FP
U800: ESP32-C6-MINI-1; MPN ESP32-C6-MINI-1-N4

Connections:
+3V3_RADIO_SW: C801.1, C802.1, C803.1, R800.1, R802.1, R804.1, R807.1, U800.3 (3V3); also elsewhere on the board
/Buttons and LEDs/ESP_APA_CLK: U800.10 (IO5); also elsewhere on the board
/Buttons and LEDs/ESP_APA_DATA: U800.9 (IO4); also elsewhere on the board
/ESP32-C6 radio/ESP_BOOT: R803.1; also elsewhere on the board
/ESP32-C6 radio/ESP_BOOT_NODE: J800.6, R802.2, R803.2, SW801.1, U800.23 (IO9)
/ESP32-C6 radio/ESP_EN: R801.1; also elsewhere on the board
/ESP32-C6 radio/ESP_GPIO8_STRAP: R804.2, U800.22 (IO8)
/ESP32-C6 radio/ESP_HOST_WAKE: U800.12 (IO0); also elsewhere on the board
/ESP32-C6 radio/ESP_PROG_VTREF: J800.1, R807.2
/ESP32-C6 radio/ESP_UART_CTS: R806.1; also elsewhere on the board
/ESP32-C6 radio/ESP_UART_CTS_NODE: R806.2, U800.6 (IO3)
/ESP32-C6 radio/ESP_UART_RTS: U800.5 (IO2); also elsewhere on the board
/ESP32-C6 radio/ESP_UART_RX: J800.4, U800.31 (TXD0); also elsewhere on the board
/ESP32-C6 radio/ESP_UART_TX: R805.1; also elsewhere on the board
/ESP32-C6 radio/ESP_UART_TX_NODE: J800.3, R805.2, U800.30 (RXD0)

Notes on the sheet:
ESP32-C6 radio and programming
Place 100nF/10uF/47uF at the module supply pins. J800 is isolated from STM TX by R805. Keep the antenna keep-out clear.
ESP_EN and ESP_BOOT must be driven open-drain by STM32 firmware; series resistors preserve reset straps.
J800.1 is level-reference sensing only: do not use the programmer to power the radio rail. R807 limits accidental backfeed.
POWER SEQUENCE: set ESP_UART_TX/CTS, ESP_EN and ESP_BOOT low or Hi-Z before RADIO_EN=0; do not drive them until +3V3_RADIO_SW is valid.
